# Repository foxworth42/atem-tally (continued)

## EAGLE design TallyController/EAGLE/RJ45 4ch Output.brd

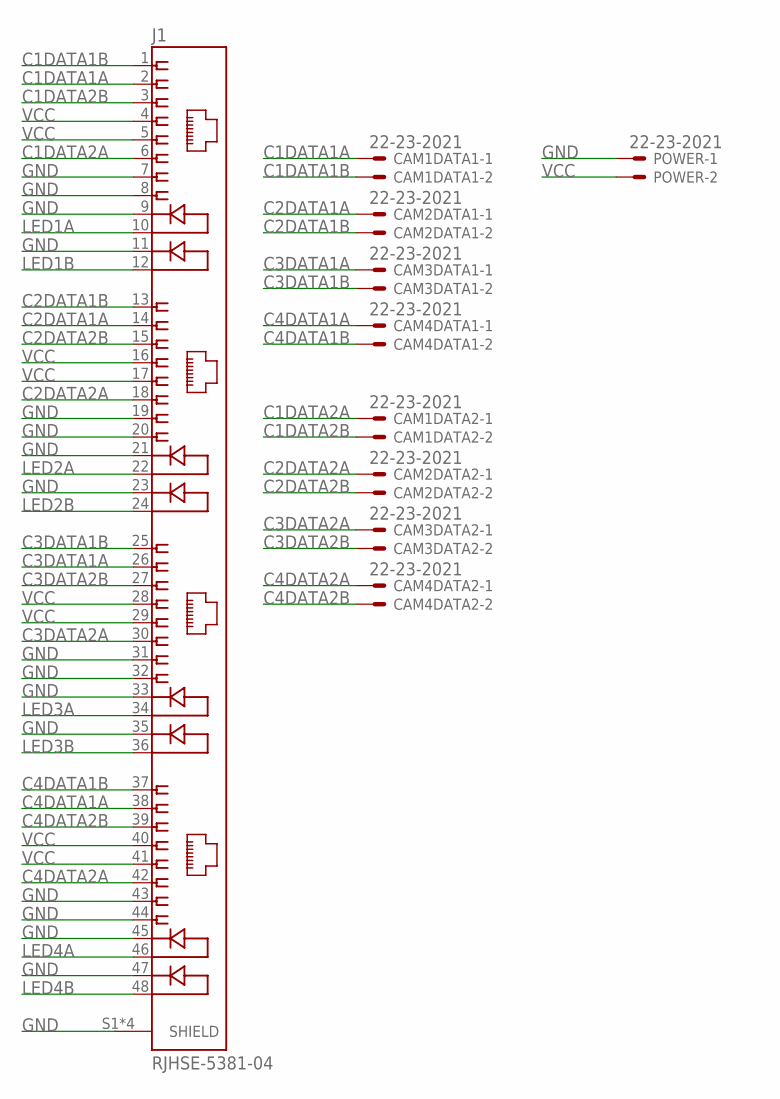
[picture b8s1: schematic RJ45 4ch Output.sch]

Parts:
CAM1DATA1, CAM1DATA2, CAM2DATA1, CAM2DATA2, CAM3DATA1, CAM3DATA2, CAM4DATA1, CAM4DATA2: 22-23-2021
J1: RJHSE-5381-04; AMPHENOL_RJHSE-5381-04
POWER: 22-23-2021

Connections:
C1DATA1A: CAM1DATA1.1, J1.2
C1DATA1B: CAM1DATA1.2, J1.1
C1DATA2A: CAM1DATA2.1, J1.6
C1DATA2B: CAM1DATA2.2, J1.3
C2DATA1A: CAM2DATA1.1, J1.14
C2DATA1B: CAM2DATA1.2, J1.13
C2DATA2A: CAM2DATA2.1, J1.18
C2DATA2B: CAM2DATA2.2, J1.15
C3DATA1A: CAM3DATA1.1, J1.26
C3DATA1B: CAM3DATA1.2, J1.25
C3DATA2A: CAM3DATA2.1, J1.30
C3DATA2B: CAM3DATA2.2, J1.27
C4DATA1A: CAM4DATA1.1, J1.38
C4DATA1B: CAM4DATA1.2, J1.37
C4DATA2A: CAM4DATA2.1, J1.42
C4DATA2B: CAM4DATA2.2, J1.39
GND: J1.7, J1.8, J1.9, J1.11, J1.19, J1.20, J1.21, J1.23, J1.31, J1.32, J1.33, J1.35, J1.43, J1.44, J1.45, J1.47, J1.S1 (SHIELD), J1.S2 (SHIELD), J1.S3 (SHIELD), J1.S4 (SHIELD), POWER.1
LED1A: J1.10
LED1B: J1.12
LED2A: J1.22
LED2B: J1.24
LED3A: J1.34
LED3B: J1.36
LED4A: J1.46
LED4B: J1.48
VCC: J1.4, J1.5, J1.16, J1.17, J1.28, J1.29, J1.40, J1.41, POWER.2

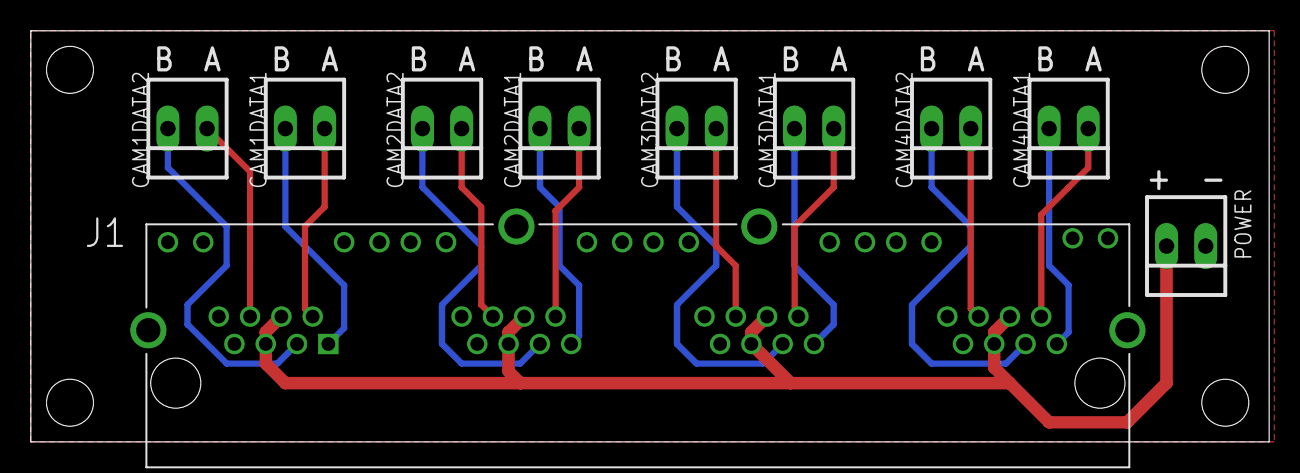
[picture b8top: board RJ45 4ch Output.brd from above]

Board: 2 copper layers, 80.3 x 26.7 mm, 10 parts (0 on the bottom side), 18 nets.

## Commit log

2019-07-26 Initial commit.
2019-07-26 Update readme.md to verify commit username is fixed.
2019-07-26 Rename files so the Arduino IDE won't complain
2019-07-26 Some general code cleanup.
2019-07-26 Add link to Skaarhoj's libraries.
2019-07-27 Initial revision of Arduino Mega shield for controller.
2019-07-27 Add some additional headers, fix switch wiring.
    Add extra I2C connector that will work with a right-angle header.
    Add a neopixel header for a possible system status light.
    Wire switch to input (missed that in the schematic)
    Trim the number of headers for holding the XBee regulated breakout to make routing easier
    Add a bunch of labels to things on the top silkscreen.
2019-07-28 Major rework of the shield to make a much better layout.
    - Expanded to 12 camera support out of the box
2019-07-28 Some code cleanup and prep work for using the controller shield.
    Also switch to using a 20x4 LCD display to be able to fit more status data.
2019-07-29 Initial revision for a 4ch RJ45 output board for the controller, and an RJ45 breakout for the on-camera light.
2019-07-29 Add some global descriptions to schematics.
2019-07-29 Standardize RS485 pinouts, update RJ45 pinouts.
    Fix pin assignments for the RS485 interconnects to standardize on pin1 = data-.
    Update the RJ45 breakouts to be mostly pin compatible with DMX over ethernet wiring standard (using pin 5/6 for V+)
    Create an XLR RS485 breakout option for wiring cameras together using 3pin DMX cables
2019-07-29 Create XLR-M breakout.
2019-07-29 Re-arrange components on controller shield to interfere less with the ethernet jack.
    Creat a quick power distro for the output boards.
2019-07-29 Update RJ45 boards to use RJHSE Amphenol jacks
2019-07-29 Add bottom silkscreen.
2019-07-31 Add notes to schematic. Code cleanup of sketch.
2019-07-31 Clean up directory names.
2019-08-01 Slim down some spacings to possibly use some 8 pin headers instead of 4x 2pin. Fix hole drill sizes.
2019-08-01 New design for RS485->Neopixel adapter with same width dimension as RJ45 breakout.
2019-08-01 Update silkscreen
2019-08-02 Add external power input to power all the external bits. Fix DRC errors that I didn't catch for some reason.
2019-08-02 May as well make the VCC line from the external power thicc
2019-08-07 Various code tweaks and cleanup.
2019-08-07 New on-camera board sized to fit Hammond 1551H enclosures.
    New version of tally shield using some SMD components, and exposing two
    serial interfaces for possible usage.
    Remove the XLR breakouts, they were just speculative.
2019-08-08 Some more designs to fit different Hammond enclosures.
2019-08-08 Extend delay on XBee writes.
2019-08-15 Go through and fix notation on RS485 wiring everywhere to use the standard A/B notation.
2019-08-15 Fix the non SMD version of the controller as well.
    Also add pads for terminators at the controller.
2019-08-15 Shift the RS485 drivers so they're aligned consistently
2019-08-19 Revisions to SMD version of controller board. Create board for wireless tally. Code revisions to sketch.
2019-08-19 Quick tweaks
2019-08-19 Update filename to reflect the enclosure type.
2019-08-19 Adjust large hole drill size. Add additional text to silkscreen.
2019-09-02 Revisions to boards after working with initial prototypes.
    - Update boards to use SMD components to help save on space.
    - Redesign wireless receiver to use 3.3v logic to avoid using the Xbee breakout.
    - Remove designs that aren't going to be used.
2019-09-02 Remove old original prototype.
2019-09-04 Update to automatically determine the maximum number of tally light sources.
2019-11-27 Tweaks to controller and wireless receiver after field test.
2019-11-28 Minor tweaks for ethernet mega.
2019-11-28 Create Arduino sketch for ATEM kill switch.
2019-11-28 Add README.
2019-11-28 Update tally controller readme too.
2019-12-03 Update kill switch to send constant commands when killswitch engaged.
    To require manual intervention to recover.
2019-12-13 Add guards to header. Update check for max cameras to only run once.
2019-12-29 Add decoupling caps to shield.
    Remove non-SMD version of shield (no-longer being worked on).
2019-12-30 Add example build images of tally system.
2019-12-30 Add serial port configuration/EEPROM storage of IP configuration info.
2020-01-01 Add decoupling caps
2020-01-01 Fix error.
2020-01-01 Working POC for supporting multiple wireless tally boxes.
    Sorta works, but there is a ~3/4-1s delay in updating the wireless boxes, haven't
    been able to determine if it's a blockage at the sender, or the receiver. Need to
    also come up with error detection to prevent the wireless lights from flickering
    randomly due to bad packets.
2020-01-05 Fix issue with controller thinking there are 0 cameras.`
2020-01-13 Add optional AREF jumper. Remove unused nets.
2020-05-03 Add BOM information for tally controller.
2020-05-03 Update buck converter link.
2020-09-08 Add ability to configure which camera has the remote/wireless tally light.
2020-09-08 Add note for configuring remote camera #
